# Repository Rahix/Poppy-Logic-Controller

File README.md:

<h2 align="center">Poppy Logic Controller</h2>

---

The _Poppy Logic Controller_ is a budget PLC (Programmable Logic Controller).
Importantly, it is only an I/O board without any PLC programming environment
(so far).  It isn't designed to be super robust but instead to use minimal
components while still staying compatible with standard industrial 24V DC
control systems.

I release the _Poppy Logic Controller_ as open hardware in hopes that others
who need a cheap solution for controlling industrial 24V DC equipment find it
useful.  _This is not a commercially viable PLC alternative._

If you want to know more about the background of this project and details of
the design, you might be interested in the blog post I wrote about it: [**Poppy
Logic Controller**][poppy-blog]

### Features
- Designed for 24V DC systems as most commonly found in modern controls
  applications.
- 16 DI (digital inputs) in a **Sinking Input** configuration.
- 16 DO (digital outputs) in a **Sinking Output** configuration.
- Firmware stubs in [Rust][fw-rust], [MicroPython][fw-mp], and [IEC 61131-3
  _Structured Text_][fw-iec].

<small>Learn more about sinking/sourcing I/O [here][realpars-input] and
[here][realpars-output] or from [my blog-post about this
project][poppy-blog].</small>

### Non-Features
- I/Os are **not** galvanically isolated.  Honestly, the isolators would
  probably be more expensive than the MCU so there is not much incentive to
  implement isolation anyway.
- The board currently does not have any communication interfaces apart from the
  Pico's USB port.  If you need to interface with anything, you might need to
  either update the board design or connect an additional mod onto the `J12`
  header.

### Building Your Own
Rendered versions of the schematic and BOM can be found here:

- [Rendered Schematic](./Docs/PoppyIO.pdf)
- [Rendered BOM](https://rahix.github.io/Poppy-Logic-Controller/Docs/PoppyIO_bom_D.html)
- [Rendered Interactive BOM](https://rahix.github.io/Poppy-Logic-Controller/Docs/PoppyIO_ibom_D.html)

#### Parts
Supplier for almost all parts of this project was [Reichelt Elektronik] (no
affiliation or sponsorship here, purely personal choice).  I've tried
reconstructing the BOM with all the Reichelt SKUs so you can painlessly get all
you need from one place if you so desire.  There is a column in the BOMs linked
above with all the information you need.

#### Additional Components
Beyond the PCB's BOM, you will need a few more components.  After all, you
probably want the nice feeling of mounting your controller on a DIN-rail, don't
you?

1. The enclosure, which is an `APRA-NORM 449-360-65` (Reichelt `APRA DB6 OBK`)
2. Optionally, a lid for the enclosure, like `APRA-NORM 449-360-12` (Reichelt
   `APRA 449-360-12`). Also available in other colors.
3. A few (2) jumpers (Reichelt `JUMPER 2,54 SW`)

#### Hardware Revisions
In the design files, you'll find the latest revision **D**.  I suggest using
that one although it is not exactly the version I have built.  My (2) boards
are built from revision **B** with one populated like revision **C** and one
populated like revision **D**.  You can read the [changelog][poppy-changelog]
for details of the differences.

#### Programming It
This repository contains a bare-bones firmware in Rust and MicroPython to get
started.  Or, if you have a background in automation, you can program the Poppy
Logic Controller in _ST_ (_Structured Text_) using the IEC 61131-3 firmware.
Check the READMEs for more info on that:

- [Firmware-Rust][fw-rust]
- [Firmware-MicroPython][fw-mp]
- [Firmware-IEC][fw-iec]

#### Not using the Pico
If you need a different microcontroller, you can drop the Raspberry Pi Pico and
instead solder the `J12` header.  You can then connect whatever controller you
desire and use the I²C bus (and interrupt lines) to interact with the I/O.

---

If you want to build your own but you are unsure or you have questions about
anything, feel free to contact me to get it sorted out!

## License
- The hardware design files (everything in `Hardware/`) are licensed under the
  [CERN-OHL-W](LICENSE-HARDWARE).
- The firmware stubs (everything in `Firmware-*/`) are licensed under
  [MIT](LICENSE-SOFTWARE).

[Reichelt Elektronik]: https://www.reichelt.de/
[poppy-blog]: https://blog.rahix.de/poppy-logic-controller/
[poppy-changelog]: ./Hardware/PoppyIO/CHANGELOG.md
[realpars-input]: https://realpars.com/sinking-and-sourcing/
[realpars-output]: https://realpars.com/sinking-output/
[fw-rust]: ./Firmware-Rust/
[fw-mp]: ./Firmware-MicroPython/
[fw-iec]: ./Firmware-IEC/

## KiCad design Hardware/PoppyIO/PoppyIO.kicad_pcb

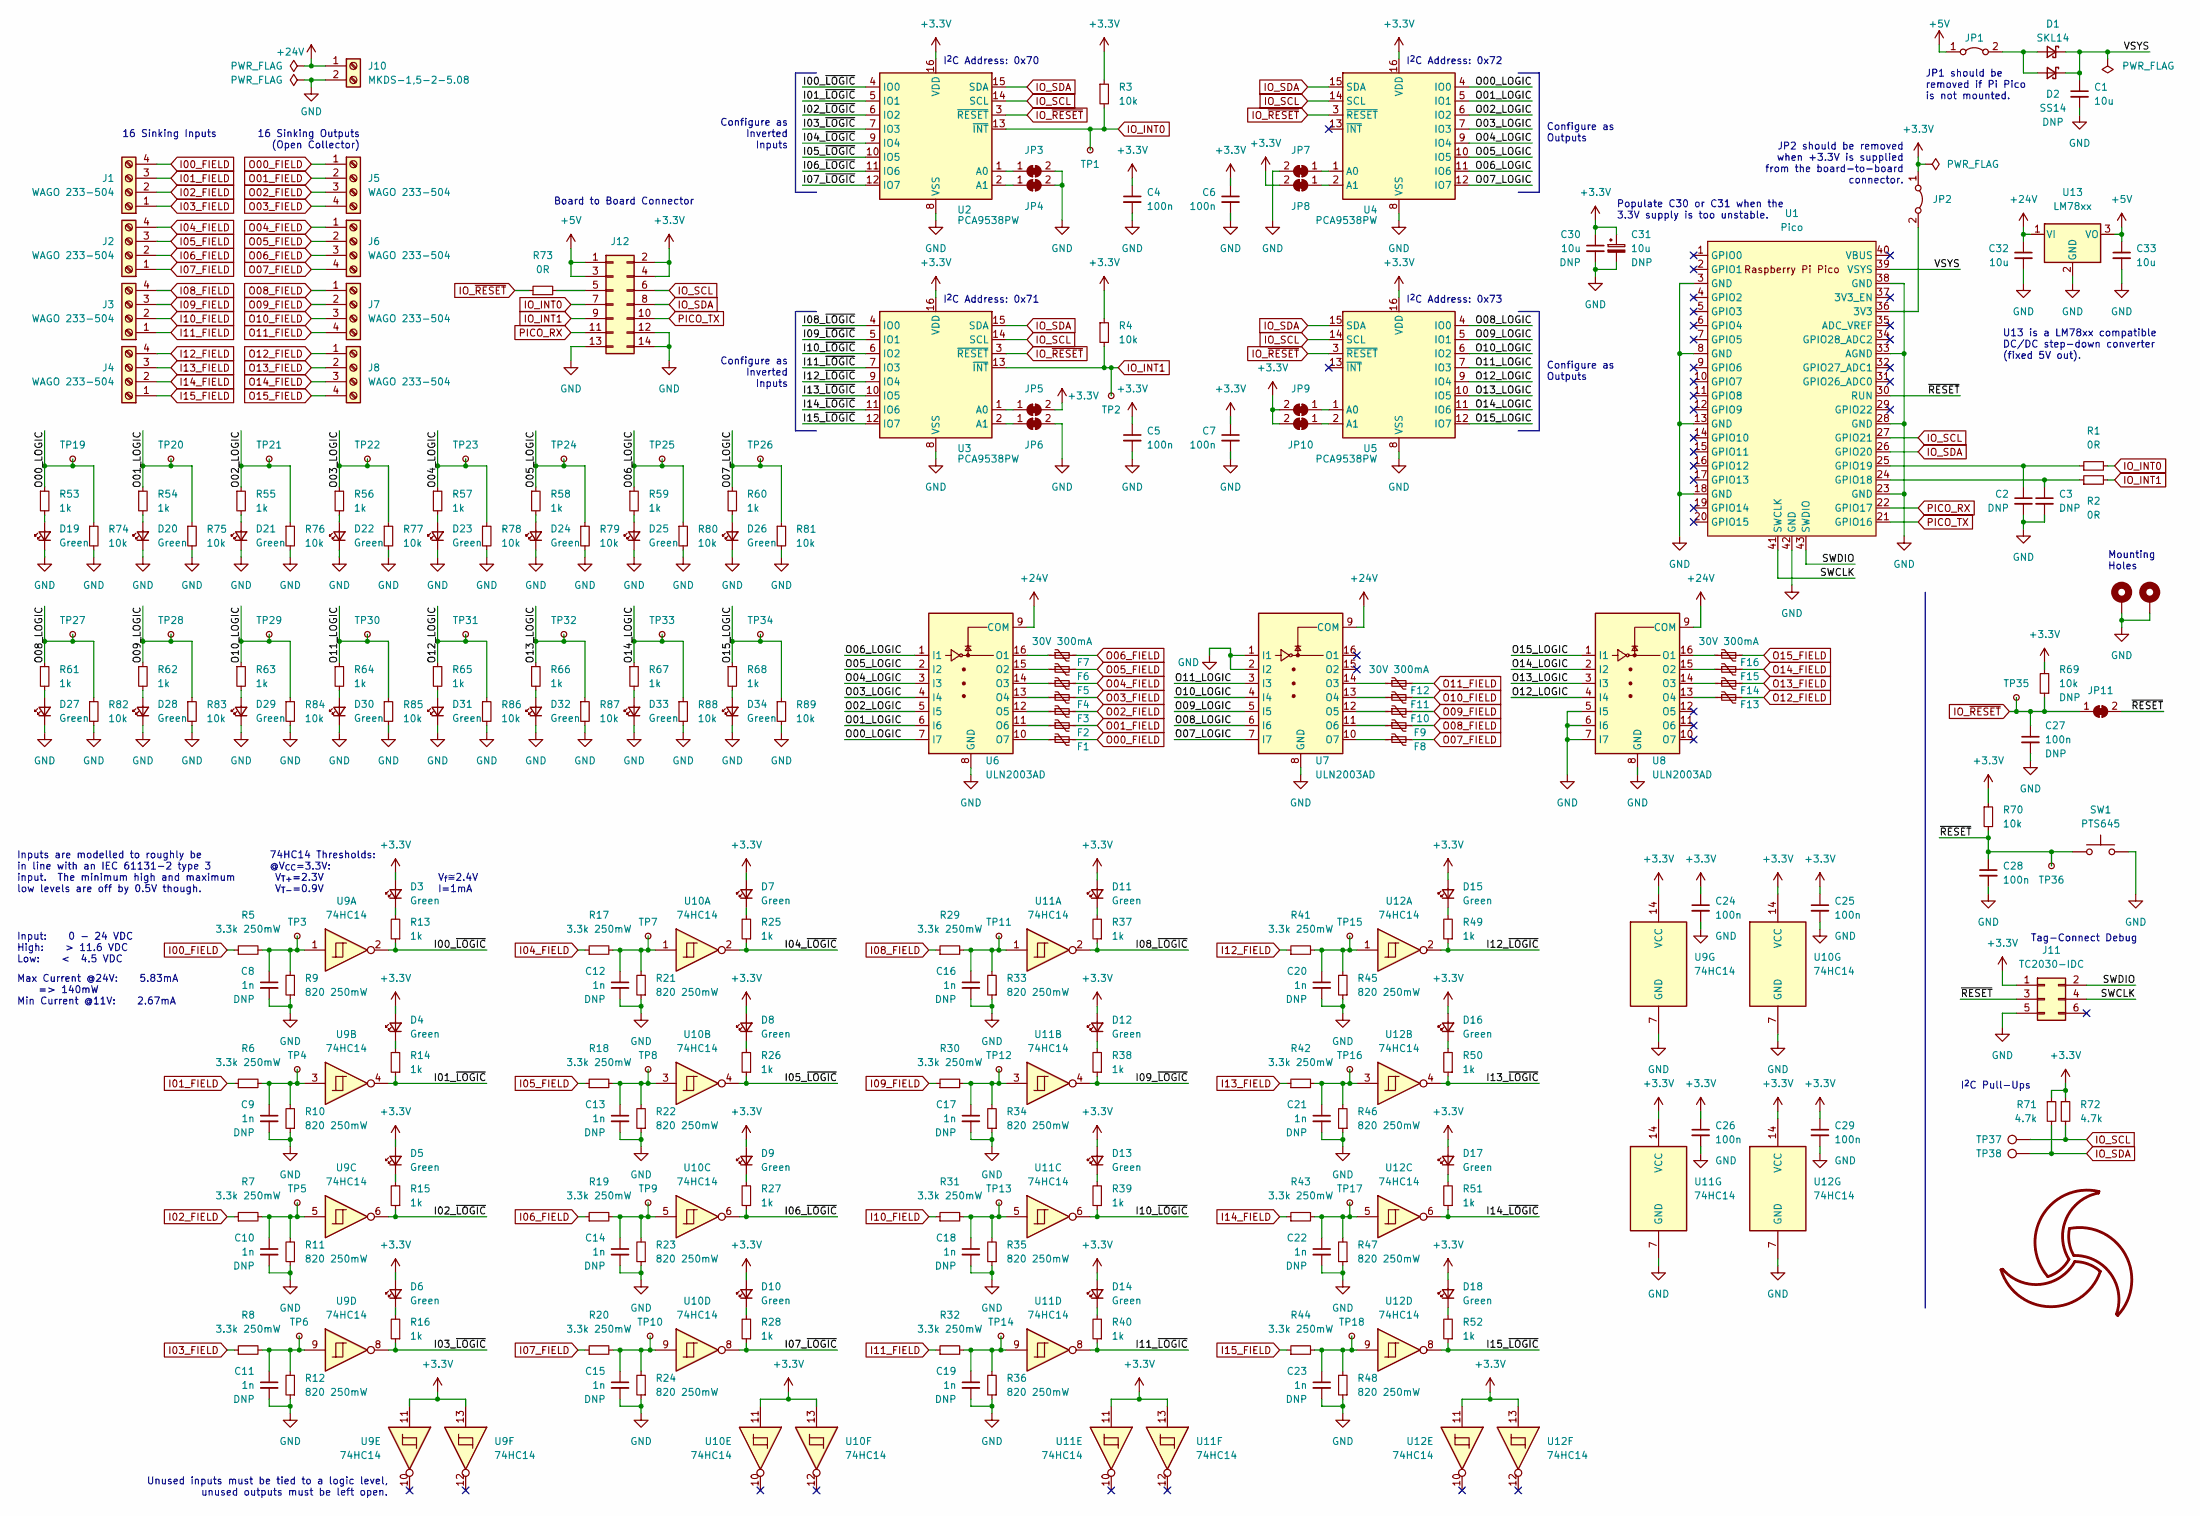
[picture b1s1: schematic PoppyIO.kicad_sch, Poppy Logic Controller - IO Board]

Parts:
C1, C30, C32, C33: 10u; C_1210_3225Metric
C2, C3: C_0603_1608Metric_Pad1.08x0.95mm_HandSolder
C4, C5, C6, C7, C24, C25, C26, C27, C28, C29: 100n; C_0603_1608Metric_Pad1.08x0.95mm_HandSolder
C8, C9, C10, C11, C12, C13, C14, C15, C16, C17, C18, C19, C20, C21, C22, C23: 1n; C_0805_2012Metric
C31: 10u; CP_Radial_D5.0mm_P2.50mm
D1: SKL14; D_SOD-123
D2: SS14; D_SMA
D3, D4, D5, D6, D7, D8, D9, D10, D11, D12, D13, D14, D15, D16, D17, D18, D19, D20, D21, D22, D23, D24, D25, D26, D27, D28, D29, D30, D31, D32, D33, D34: Green; LED_0805_2012Metric_Pad1.15x1.40mm_HandSolder
F1, F2, F3, F4, F5, F6, F7, F8, F9, F10, F11, F12, F13, F14, F15, F16: 30V 300mA; Fuse_1210_3225Metric_Pad1.42x2.65mm_HandSolder
H1, H2: MountingHole_Pad; MountingHole_3.2mm_M3_Pad_Via
J1, J2, J3, J4, J5, J6, J7, J8: WAGO 233-504; WAGO_233-204
J10: MKDS-1,5-2-5.08; TerminalBlock_Phoenix_MKDS-1,5-2-5.08_1x02_P5.08mm_Horizont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
J11: TC2030-IDC; Tag-Connect_TC2030-IDC-FP_2x03_P1.27mm_Vertical
J12: Conn_02x07_Odd_Even; IDC-Header_2x07_P2.54mm_Vertical
JP1, JP2: PinHeader_1x02_P2.54mm_Vertical
JP3, JP4, JP5, JP6, JP7, JP8, JP9, JP10, JP11: SolderJumper_2_Bridged; SolderJumper-2_P1.3mm_Bridged_RoundedPad1.0x1.5mm
R1, R2, R73: 0R; R_0603_1608Metric
R3, R4, R69, R70, R74, R75, R76, R77, R78, R79, R80, R81, R82, R83, R84, R85, R86, R87, R88, R89: 10k; R_0603_1608Metric
R5, R6, R7, R8, R17, R18, R19, R20, R29, R30, R31, R32, R41, R42, R43, R44: 3.3k 250mW; R_1206_3216Metric
R9, R10, R11, R12, R21, R22, R23, R24, R33, R34, R35, R36, R45, R46, R47, R48: 820 250mW; R_1206_3216Metric
R13, R14, R15, R16, R25, R26, R27, R28, R37, R38, R39, R40, R49, R50, R51, R52, R53, R54, R55, R56, R57, R58, R59, R60, R61, R62, R63, R64, R65, R66, R67, R68: 1k; R_0603_1608Metric
R71, R72: 4.7k; R_0603_1608Metric_Pad0.98x0.95mm_HandSolder
SW1: PTS645; SW_SPST_PTS645
SYM1: SYM_Rahix
TP1, TP2, TP3, TP4, TP5, TP6, TP7, TP8, TP9, TP10, TP11, TP12, TP13, TP14, TP15, TP16, TP17, TP18, TP19, TP20, TP21, TP22, TP23, TP24, TP25, TP26, TP27, TP28, TP29, TP30, TP31, TP32, TP33, TP34, TP35, TP36: TestPoint_Small; TestPoint_Pad_D1.5mm
TP37, TP38: TestPoint; TestPoint_Pad_D1.5mm
U1: Pico; RPi_Pico_SMD_TH
U2, U3, U4, U5: PCA9538PW; TSSOP-16_4.4x5mm_P0.65mm
U6, U7, U8: ULN2003AD; SOIC-16_3.9x9.9mm_P1.27mm
U9, U10, U11, U12: 74HC14; SOIC-14_3.9x8.7mm_P1.27mm
U13: LM78xx; TO-220-3_Vertical_Clearance

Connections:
+3.3V: C4.1, C5.1, C6.1, C7.1, C24.1, C25.1, C26.1, C29.1, C30.1, C31.1, D3.2 (A), D4.2 (A), D5.2 (A), D6.2 (A), D7.2 (A), D8.2 (A), D9.2 (A), D10.2 (A), D11.2 (A), D12.2 (A), D13.2 (A), D14.2 (A), D15.2 (A), D16.2 (A), D17.2 (A), D18.2 (A), J11.1, J12.2, J12.4, JP2.1 (A), JP5.2 (B), JP8.2 (B), JP9.2 (B), JP10.2 (B), R3.1, R4.1, R69.2, R70.1, R71.1, R72.1, U2.16 (VDD), U3.16 (VDD), U4.16 (VDD), U5.16 (VDD), U9.11, U9.13, U9.14 (VCC), U10.11, U10.13, U10.14 (VCC), U11.11, U11.13, U11.14 (VCC), U12.11, U12.13, U12.14 (VCC)
+5V: C33.1, J12.1, J12.3, JP1.1 (A), U13.3 (VO)
+24V: C32.1, J10.1, U6.9 (COM), U7.9 (COM), U8.9 (COM), U13.1 (VI)
/I00_~LOGIC: R13.1, U2.4 (IO0), U9.2
/I01_~LOGIC: R14.1, U2.5 (IO1), U9.4
/I02_~LOGIC: R15.1, U2.6 (IO2), U9.6
/I03_~LOGIC: R16.1, U2.7 (IO3), U9.8
/I04_~LOGIC: R25.1, U2.9 (IO4), U10.2
/I05_~LOGIC: R26.1, U2.10 (IO5), U10.4
/I06_~LOGIC: R27.1, U2.11 (IO6), U10.6
/I07_~LOGIC: R28.1, U2.12 (IO7), U10.8
/I08_~LOGIC: R37.1, U3.4 (IO0), U11.2
/I09_~LOGIC: R38.1, U3.5 (IO1), U11.4
/I10_~LOGIC: R39.1, U3.6 (IO2), U11.6
/I11_~LOGIC: R40.1, U3.7 (IO3), U11.8
/I12_~LOGIC: R49.1, U3.9 (IO4), U12.2
/I13_~LOGIC: R50.1, U3.10 (IO5), U12.4
/I14_~LOGIC: R51.1, U3.11 (IO6), U12.6
/I15_~LOGIC: R52.1, U3.12 (IO7), U12.8
/O00_LOGIC: R53.1, R74.1, TP19.1, U4.4 (IO0), U6.7 (I7)
/O01_LOGIC: R54.1, R75.1, TP20.1, U4.5 (IO1), U6.6 (I6)
/O02_LOGIC: R55.1, R76.1, TP21.1, U4.6 (IO2), U6.5 (I5)
/O03_LOGIC: R56.1, R77.1, TP22.1, U4.7 (IO3), U6.4 (I4)
/O04_LOGIC: R57.1, R78.1, TP23.1, U4.9 (IO4), U6.3 (I3)
/O05_LOGIC: R58.1, R79.1, TP24.1, U4.10 (IO5), U6.2 (I2)
/O06_LOGIC: R59.1, R80.1, TP25.1, U4.11 (IO6), U6.1 (I1)
/O07_LOGIC: R60.1, R81.1, TP26.1, U4.12 (IO7), U7.7 (I7)
/O08_LOGIC: R61.1, R82.1, TP27.1, U5.4 (IO0), U7.6 (I6)
/O09_LOGIC: R62.1, R83.1, TP28.1, U5.5 (IO1), U7.5 (I5)
/O10_LOGIC: R63.1, R84.1, TP29.1, U5.6 (IO2), U7.4 (I4)
/O11_LOGIC: R64.1, R85.1, TP30.1, U5.7 (IO3), U7.3 (I3)
/O12_LOGIC: R65.1, R86.1, TP31.1, U5.9 (IO4), U8.4 (I4)
/O13_LOGIC: R66.1, R87.1, TP32.1, U5.10 (IO5), U8.3 (I3)
/O14_LOGIC: R67.1, R88.1, TP33.1, U5.11 (IO6), U8.2 (I2)
/O15_LOGIC: R68.1, R89.1, TP34.1, U5.12 (IO7), U8.1 (I1)
/SWCLK: J11.4, U1.41 (SWCLK)
/SWDIO: J11.2, U1.43 (SWDIO)
/VSYS: C1.1, D1.1 (K), D2.1 (K), U1.39 (VSYS)
/~RESET: C28.1, J11.3, JP11.2 (B), R70.2, SW1.1, TP36.1, U1.30 (RUN)
GND: C1.2, C2.2, C3.2, C4.2, C5.2, C6.2, C7.2, C8.2, C9.2, C10.2, C11.2, C12.2, C13.2, C14.2, C15.2, C16.2, C17.2, C18.2, C19.2, C20.2, C21.2, C22.2, C23.2, C24.2, C25.2, C26.2, C27.2, C28.2, C29.2, C30.2, C31.2, C32.2, C33.2, D19.1 (K), D20.1 (K), D21.1 (K), D22.1 (K), D23.1 (K), D24.1 (K), D25.1 (K), D26.1 (K), D27.1 (K), D28.1 (K), D29.1 (K), D30.1 (K), D31.1 (K), D32.1 (K), D33.1 (K), D34.1 (K), H1.1, H2.1, J10.2, J11.5, J12.12, J12.13, J12.14, JP3.2 (B), JP4.2 (B), JP6.2 (B), JP7.2 (B), R9.1, R10.1, R11.1, R12.1, R21.1, R22.1, R23.1, R24.1, R33.1, R34.1, R35.1, R36.1, R45.1, R46.1, R47.1, R48.1, R74.2, R75.2, R76.2, R77.2, R78.2, R79.2, R80.2, R81.2, R82.2, R83.2, R84.2, R85.2, R86.2, R87.2, R88.2, R89.2, SW1.2, U1.3 (GND), U1.8 (GND), U1.13 (GND), U1.18 (GND), U1.23 (GND), U1.28 (GND), U1.33 (AGND), U1.38 (GND), U1.42 (GND), U2.8 (VSS), U3.8 (VSS), U4.8 (VSS), U5.8 (VSS), U6.8 (GND), U7.1 (I1), U7.2 (I2), U7.8 (GND), U8.5 (I5), U8.6 (I6), U8.7 (I7), U8.8 (GND), U9.7 (GND), U10.7 (GND), U11.7 (GND), U12.7 (GND), U13.2 (GND)
I00_FIELD: J1.4, R5.1
I01_FIELD: J1.3, R6.1
I02_FIELD: J1.2, R7.1
I03_FIELD: J1.1, R8.1
I04_FIELD: J2.4, R17.1
I05_FIELD: J2.3, R18.1
I06_FIELD: J2.2, R19.1
I07_FIELD: J2.1, R20.1
I08_FIELD: J3.4, R29.1
I09_FIELD: J3.3, R30.1
I10_FIELD: J3.2, R31.1
I11_FIELD: J3.1, R32.1
I12_FIELD: J4.4, R41.1
I13_FIELD: J4.3, R42.1
I14_FIELD: J4.2, R43.1
I15_FIELD: J4.1, R44.1
IO_INT0: J12.7, R1.2, R3.2, TP1.1, U2.13 (~INT)
IO_INT1: J12.9, R2.2, R4.2, TP2.1, U3.13 (~INT)
IO_SCL: J12.6, R72.2, TP37.1, U1.27 (GPIO21), U2.14 (SCL), U3.14 (SCL), U4.14 (SCL), U5.14 (SCL)
IO_SDA: J12.8, R71.2, TP38.1, U1.26 (GPIO20), U2.15 (SDA), U3.15 (SDA), U4.15 (SDA), U5.15 (SDA)
IO_~RESET: C27.1, JP11.1 (A), R69.1, R73.1, TP35.1, U2.3 (~RESET), U3.3 (~RESET), U4.3 (~RESET), U5.3 (~RESET)
unnamed: C2.1, R1.1, U1.25 (GPIO19)
unnamed: C3.1, R2.1, U1.24 (GPIO18)
unnamed: C8.1, R5.2, R9.2, TP3.1, U9.1
unnamed: C9.1, R6.2, R10.2, TP4.1, U9.3
unnamed: C10.1, R7.2, R11.2, TP5.1, U9.5
unnamed: C11.1, R8.2, R12.2, TP6.1, U9.9
unnamed: C12.1, R17.2, R21.2, TP7.1, U10.1
unnamed: C13.1, R18.2, R22.2, TP8.1, U10.3
unnamed: C14.1, R19.2, R23.2, TP9.1, U10.5
unnamed: C15.1, R20.2, R24.2, TP10.1, U10.9
unnamed: C16.1, R29.2, R33.2, TP11.1, U11.1
unnamed: C17.1, R30.2, R34.2, TP12.1, U11.3
unnamed: C18.1, R31.2, R35.2, TP13.1, U11.5
unnamed: C19.1, R32.2, R36.2, TP14.1, U11.9
unnamed: C20.1, R41.2, R45.2, TP15.1, U12.1
unnamed: C21.1, R42.2, R46.2, TP16.1, U12.3
unnamed: C22.1, R43.2, R47.2, TP17.1, U12.5
unnamed: C23.1, R44.2, R48.2, TP18.1, U12.9
unnamed: D1.2 (A), D2.2 (A), JP1.2 (B)
unnamed: D3.1 (K), R13.2
unnamed: D4.1 (K), R14.2
unnamed: D5.1 (K), R15.2
unnamed: D6.1 (K), R16.2
unnamed: D7.1 (K), R25.2
unnamed: D8.1 (K), R26.2
unnamed: D9.1 (K), R27.2
unnamed: D10.1 (K), R28.2
unnamed: D11.1 (K), R37.2
unnamed: D12.1 (K), R38.2
unnamed: D13.1 (K), R39.2
unnamed: D14.1 (K), R40.2
unnamed: D15.1 (K), R49.2
unnamed: D16.1 (K), R50.2
unnamed: D17.1 (K), R51.2
unnamed: D18.1 (K), R52.2
unnamed: D19.2 (A), R53.2
unnamed: D20.2 (A), R54.2
unnamed: D21.2 (A), R55.2
unnamed: D22.2 (A), R56.2
unnamed: D23.2 (A), R57.2
unnamed: D24.2 (A), R58.2
unnamed: D25.2 (A), R59.2
unnamed: D26.2 (A), R60.2
unnamed: D27.2 (A), R61.2
unnamed: D28.2 (A), R62.2
unnamed: D29.2 (A), R63.2
unnamed: D30.2 (A), R64.2
unnamed: D31.2 (A), R65.2
unnamed: D32.2 (A), R66.2
unnamed: D33.2 (A), R67.2
unnamed: D34.2 (A), R68.2
unnamed: F1.1, U6.10 (O7)
unnamed: F2.1, U6.11 (O6)
unnamed: F3.1, U6.12 (O5)
unnamed: F4.1, U6.13 (O4)
unnamed: F5.1, U6.14 (O3)
unnamed: F6.1, U6.15 (O2)
unnamed: F7.1, U6.16 (O1)
unnamed: F8.1, U7.10 (O7)
unnamed: F9.1, U7.11 (O6)
unnamed: F10.1, U7.12 (O5)
unnamed: F11.1, U7.13 (O4)
unnamed: F12.1, U7.14 (O3)
unnamed: F13.1, U8.13 (O4)
unnamed: F14.1, U8.14 (O3)
unnamed: F15.1, U8.15 (O2)
unnamed: F16.1, U8.16 (O1)
unnamed: J12.5, R73.2
unnamed: JP2.2 (B), U1.36 (3V3)
unnamed: JP3.1 (A), U2.1 (A0)
unnamed: JP4.1 (A), U2.2 (A1)
unnamed: JP5.1 (A), U3.1 (A0)
unnamed: JP6.1 (A), U3.2 (A1)
unnamed: JP7.1 (A), U4.1 (A0)
unnamed: JP8.1 (A), U4.2 (A1)
unnamed: JP9.1 (A), U5.1 (A0)
unnamed: JP10.1 (A), U5.2 (A1)
O00_FIELD: F1.2, J5.1
O01_FIELD: F2.2, J5.2
O02_FIELD: F3.2, J5.3
O03_FIELD: F4.2, J5.4
O04_FIELD: F5.2, J6.1
O05_FIELD: F6.2, J6.2
O06_FIELD: F7.2, J6.3
O07_FIELD: F8.2, J6.4
O08_FIELD: F9.2, J7.1
O09_FIELD: F10.2, J7.2
O10_FIELD: F11.2, J7.3
O11_FIELD: F12.2, J7.4
O12_FIELD: F13.2, J8.1
O13_FIELD: F14.2, J8.2
O14_FIELD: F15.2, J8.3
O15_FIELD: F16.2, J8.4
PICO_RX: J12.11, U1.22 (GPIO17)
PICO_TX: J12.10, U1.21 (GPIO16)

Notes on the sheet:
Configure as Outputs
16 Sinking Inputs
Input: 0 - 24 VDC High: > 11.6 VDC Low: < 4.5 VDC
U13 is a LM78xx compatible DC/DC step-down converter (fixed 5V out).
JP1 should be removed if Pi Pico is not mounted.
Inputs are modelled to roughly be in line with an IEC 61131-2 type 3 input. The minimum high and maximum low levels are off by 0.5V though.
Unused inputs must be tied to a logic level, unused outputs must be left open.
I^{2}C Address: 0x70
I^{2}C Address: 0x73
I^{2}C Address: 0x72
74HC14 Thresholds: @V_{CC}=3.3V: V_{T+}=2.3V V_{T-}=0.9V
I^{2}C Address: 0x71
Tag-Connect Debug
Max Current @24V: 5.83mA => 140mW Min Current @11V: 2.67mA
Board to Board Connector
Configure as Inverted Inputs
I^{2}C Pull-Ups
16 Sinking Outputs (Open Collector)
Populate C30 or C31 when the 3.3V supply is too unstable.
V_{f}≅2.4V I=1mA
JP2 should be removed when +3.3V is supplied from the board-to-board connector.
Mounting Holes

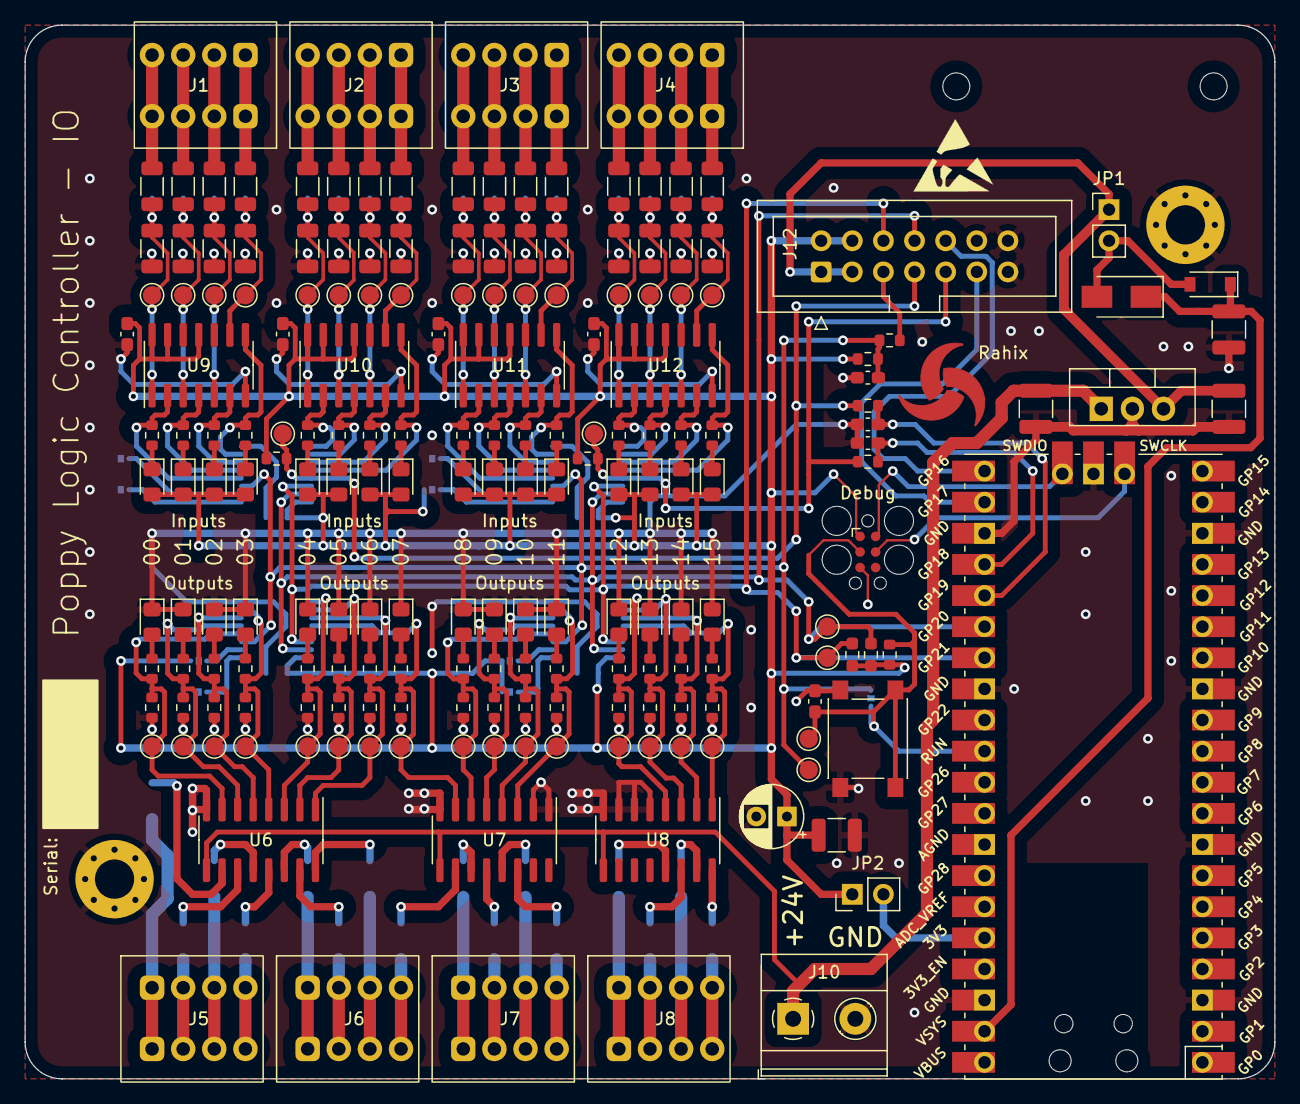
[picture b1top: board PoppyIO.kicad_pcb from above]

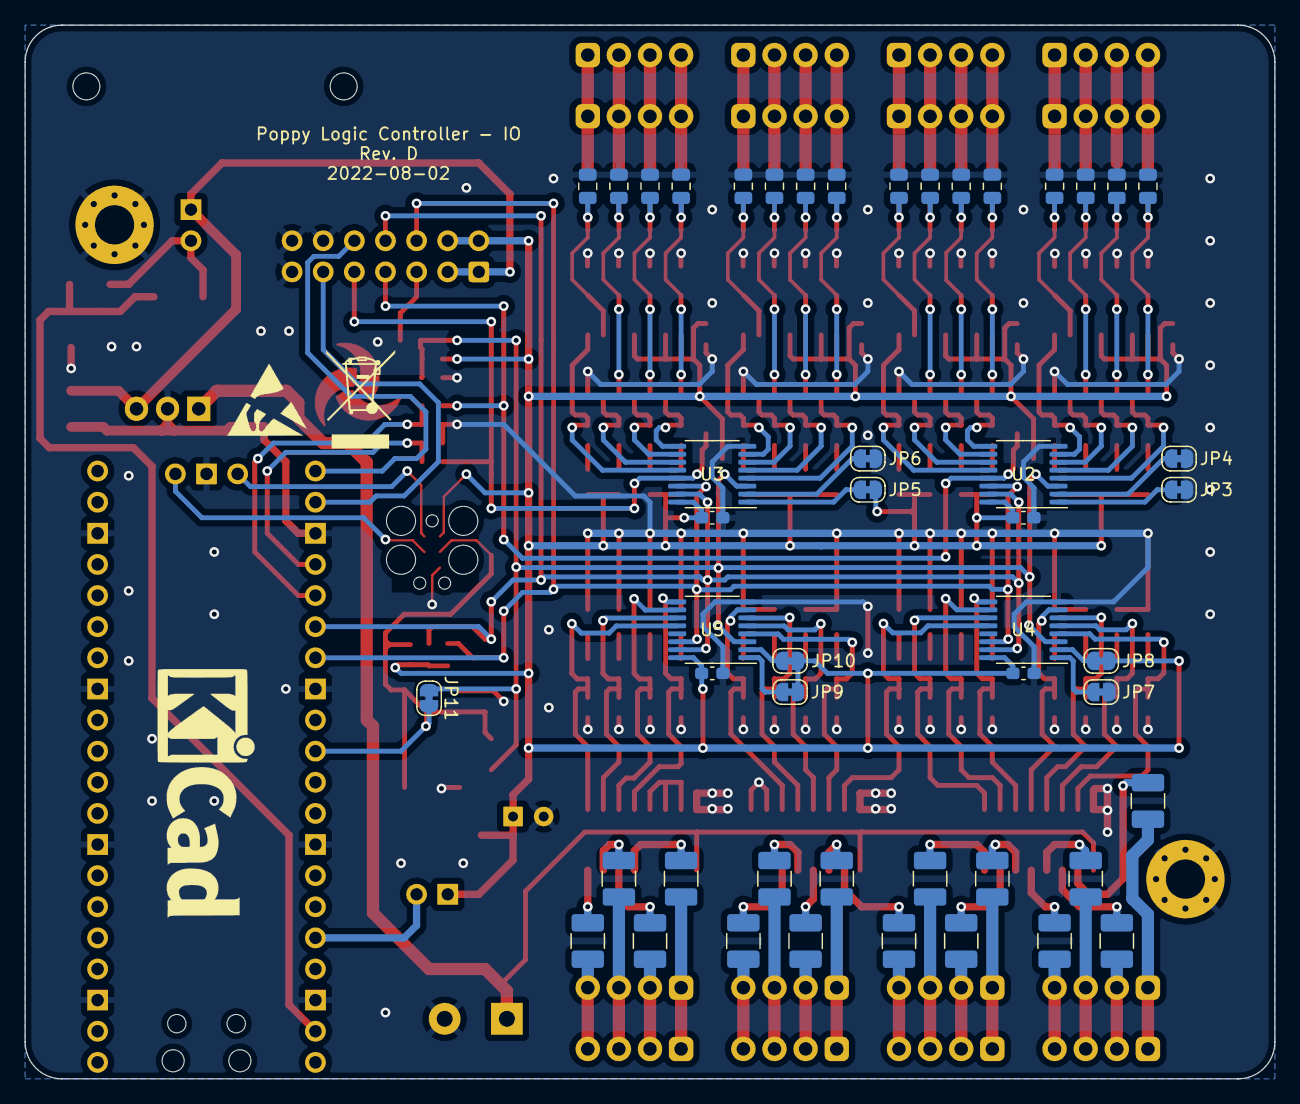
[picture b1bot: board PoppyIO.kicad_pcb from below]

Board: 2 copper layers, 102.0 x 86.0 mm, 249 parts (49 on the bottom side), 156 nets.

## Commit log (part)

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2022-04-01 Initial
2022-04-01 hw: lib: Import RP-Pico library
    Import symbols and footprints for the Raspberry-Pi Pico from
    https://github.com/ncarandini/KiCad-RP-Pico
    at commit dc6f9b9f213d ("Update Install instructions.md").
2022-04-01 hw: lib: pico: Update 3D model path
2022-04-01 hw: io: Add libraries
2022-04-01 hw: io: Work on 24 VDC inputs and outputs
2022-04-01 hw: io: Updates
2022-04-01 hw: io: Single sheet
2022-04-01 hw: io: Output drivers and other things
2022-04-01 hw: lib: Add WAGO 233-204/504 footprint
2022-04-01 hw: io: Add poppy library
2022-04-02 hw: lib: Update pico pin types
    The 3V3 pin is a power output and one GND pin was erroneously specified
    as "bidirectional".
2022-04-02 hw: io: Annotate
2022-04-02 hw: io: Footprints
2022-04-02 hw: ui: Adjust connector pin ordering
2022-04-02 hw: io: More layout improvements
    Reorder driver pins
2022-04-03 hw: lib: Use official pico 3D model
    This model is much simpler and thus loading times are much shorter.
2022-04-03 hw: io: Update footprints
2022-04-03 hw: io: Update PCB
2022-04-03 hw: io: PCB Updates
2022-04-03 hw: io: More updates
2022-04-06 hw: io: Switch to ULN2003AD
2022-04-10 hw: io: Updates & clean PCB
2022-04-13 hw: lib: Add PCA9538PW symbol
2022-04-13 hw: Update gitignore
2022-04-13 hw: io: Update schematic
    Different input stage
2022-04-14 hw: io: ERC fixes
2022-04-14 hw: io: Add KiBOM config
2022-04-14 hw: io: Update schematic
2022-04-14 hw: io: Use one more inverter IC
    This should make layout easier
2022-04-14 hw: io: Different fuses
2022-04-15 hw: io: Unused ULN2003 inputs
    Tie them to GND.
2022-04-22 hw: io: Start PCB layout for real this time
2022-04-22 hw: io: sch: Reorder series resistors for output LEDs
    This helps with routing.
2022-04-22 hw: io: Board settings
2022-04-22 hw: io: PCB layout
2022-04-22 hw: io: More PCB layout
2022-04-23 hw: io: Updae PCB and DRC fixes
2022-04-23 hw: io: Update JP2
    shouldn't be a solder jumper
2022-04-23 hw: io: Add footprints for 3V3 decoupling caps
2022-04-23 hw: io: Add artwork
2022-04-23 hw: io: More PCB tweaks
2022-04-24 hw: lib: Add footprint for TO-220-3 with clearance
    This allows to mount LM78xx regulators but also drop-in replacements
    like Gaptec's LMS78 or LMO78 DC/DC step-down supplies.
2022-04-24 hw: io: Add footprints for 24V -> 5V regulator
    In the future, maybe we will want to switch to a unified 24V supply.
    Add footprints for installing a regulator or SPMS to do this.
2022-04-24 hw: io: pcb: Fabrication layers
2022-04-24 hw: io: Final touches and prepare revision A
2022-04-25 hw: io: Switch to 14-pin IDC
2022-06-26 hw: io: Fix wrong DI resistors
    Copy-paste error - the calculations projected an 820Ω resistor but I
    accidentally used 680Ω instead. This still works but has different
    limiting values...
2022-08-02 hw: io: Schematic updates
    - Drop DNP config from LM78xx regulator and capacitors.
    - Removed screw-terminal J9 for external 5V supply.
    - Switched +24VDC screw-terminal to 2-pin variant.
    - Documented J2 meaning.
2022-08-02 hw: io: Mirror schematic changes on PCB
2022-08-02 hw: io: PCB cleanup and update J10 footprint
    Choose an appropriate screw-terminal for J10 which has 2 pins and 5.08mm
    pitch.
2022-08-02 hw: io: Add Reichelt SKUs for all applicable parts
2022-08-02 Update CHANGELOG
2022-08-06 hw: io: Generate revision D documents
    - Interactive BOM
    - HTML BOM
    - Schematic PDF
2022-08-07 fw: Add bare-bones MicroPython firmware
    This is a sample driver for writing controls programs for the Poppy
    Logic Controller in MicroPython.
2022-08-07 fw: Add bare-bones Rust firmware
    This is a sample firmware for writing a control program for the Poppy
    Logic Controller in Rust. It uses the `port-expander` [1] crate to
    interact with the I/O expanders.
    [1]: https://crates.io/crates/port-expander
2022-08-07 Revision D Rendered Documents
2022-08-07 Add README and licenses
    Document this project...
2022-08-21 Add the beginnings of an IEC firmware
    This firmware allows writing programs for the Poppy Logic Controller in
    IEC 61131-3 languages like ST (Structured Text).
2022-08-21 fw: iec: Cleanup driver implementation
2022-08-21 fw: iec: Cleanup the ST program
    Proper style and naming conventions. Add some comments.
2022-09-01 fw: iec: Integrate modbus RTU server
    The server is not connected to the PLC runtime yet so register changes
    will not have any effect. It is visible as a USB-Serial device over
    USB.
2022-09-01 fw: iec: Integrate modbus with PLC runtime
    Make memory bits %MX00 - %MX15 and memory words %MW00 - %MW15 available
    via modbus coils 0 - 15 and holding registers 0 - 15 respectively.
    Additionally, expose the state of all inputs in discrete inputs 0 - 15
    and the state of all outputs in descrete inputs 16 - 31.
2022-09-01 fw: iec: Use modbus in example code
    Add modbus coils 0 and 1 as alternative start and stop buttons which can
    be remotely controlled and have the same function as the local inputs.
2022-09-01 fw: iec: Document Modbus interface
2022-09-01 Ignore pymodbus history file
2022-09-01 fw: iec: Document Modbus GUI
2022-09-05 fw: iec: Use upstream rmodbus
2023-01-05 fw: Apply rustfmt
2023-01-05 Enable GitHub Dependabot
2023-01-05 ci: Setup GitHub Actions
2023-01-05 fw: iec: Drop unused delay timer
2023-01-05 build(deps): bump shared-bus from 0.2.4 to 0.2.5 in /Firmware-Rust
    Bumps [shared-bus](https://github.com/Rahix/shared-bus) from 0.2.4 to 0.2.5.
    - [Release notes](https://github.com/Rahix/shared-bus/releases)
    - [Changelog](https://github.com/Rahix/shared-bus/blob/main/CHANGELOG.md)
    - [Commits](https://github.com/Rahix/shared-bus/compare/v0.2.4...v0.2.5)
    ---
    updated-dependencies:
2023-01-05 build(deps): bump paste from 1.0.8 to 1.0.11 in /Firmware-IEC
    Bumps [paste](https://github.com/dtolnay/paste) from 1.0.8 to 1.0.11.
    - [Release notes](https://github.com/dtolnay/paste/releases)
    - [Commits](https://github.com/dtolnay/paste/compare/1.0.8...1.0.11)
    ---
    updated-dependencies:
    - dependency-name: paste
2023-01-05 fw: rust: Bump shared-bus from 0.2.4 to 0.2.5
2023-01-05 fw: rust: Bump cortex-m from 0.7.5 to 0.7.7
2023-01-05 fw: iec: Bump paste from 1.0.8 to 1.0.11
2023-01-05 build(deps): bump cortex-m-rt from 0.7.1 to 0.7.2 in /Firmware-Rust
    Bumps [cortex-m-rt](https://github.com/rust-embedded/cortex-m) from 0.7.1 to 0.7.2.
    - [Release notes](https://github.com/rust-embedded/cortex-m/releases)
    - [Changelog](https://github.com/rust-embedded/cortex-m/blob/master/CHANGELOG.md)
    - [Commits](https://github.com/rust-embedded/cortex-m/compare/v0.7.1...v0.7.2)
    ---
    updated-dependencies:
2023-01-05 build(deps): bump cortex-m-rt from 0.7.1 to 0.7.2 in /Firmware-IEC
    Bumps [cortex-m-rt](https://github.com/rust-embedded/cortex-m) from 0.7.1 to 0.7.2.
    - [Release notes](https://github.com/rust-embedded/cortex-m/releases)
    - [Changelog](https://github.com/rust-embedded/cortex-m/blob/master/CHANGELOG.md)
    - [Commits](https://github.com/rust-embedded/cortex-m/compare/v0.7.1...v0.7.2)
    ---
    updated-dependencies:
2023-01-05 fw: iec: Bump cortex-m-rt from 0.7.1 to 0.7.2
2023-01-05 fw: rust: Bump cortex-m-rt from 0.7.1 to 0.7.2
2023-01-05 fw: iec: Bump cc from 1.0.73 to 1.0.78
2023-01-05 build(deps): bump cortex-m from 0.7.5 to 0.7.7 in /Firmware-IEC
    Bumps [cortex-m](https://github.com/rust-embedded/cortex-m) from 0.7.5 to 0.7.7.
    - [Release notes](https://github.com/rust-embedded/cortex-m/releases)
    - [Changelog](https://github.com/rust-embedded/cortex-m/blob/v0.7.7/CHANGELOG.md)
    - [Commits](https://github.com/rust-embedded/cortex-m/compare/v0.7.5...v0.7.7)
    ---
    updated-dependencies:
2023-01-05 fw: iec: Bump cortex-m from 0.7.5 to 0.7.7
2023-01-05 dependabot: Tune settings
    Only run monthly and properly prefix commit messages.
2023-01-05 build(deps): bump rp-pico from 0.2.0 to 0.6.0 in /Firmware-Rust
    Bumps [rp-pico](https://github.com/rp-rs/rp-hal-boards) from 0.2.0 to 0.6.0.
    - [Release notes](https://github.com/rp-rs/rp-hal-boards/releases)
    - [Commits](https://github.com/rp-rs/rp-hal-boards/compare/pimoroni-servo2040-0.2.0...rp-pico-0.6.0)
    ---
    updated-dependencies:
    - dependency-name: rp-pico
2023-01-05 build(deps): bump rp-pico from 0.2.0 to 0.6.0 in /Firmware-IEC
    Bumps [rp-pico](https://github.com/rp-rs/rp-hal-boards) from 0.2.0 to 0.6.0.
    - [Release notes](https://github.com/rp-rs/rp-hal-boards/releases)
    - [Commits](https://github.com/rp-rs/rp-hal-boards/compare/pimoroni-servo2040-0.2.0...rp-pico-0.6.0)
    ---
    updated-dependencies:
    - dependency-name: rp-pico
2023-02-01 fw: iec: bump cc from 1.0.78 to 1.0.79 in /Firmware-IEC
    Bumps [cc](https://github.com/rust-lang/cc-rs) from 1.0.78 to 1.0.79.
    - [Release notes](https://github.com/rust-lang/cc-rs/releases)
    - [Commits](https://github.com/rust-lang/cc-rs/compare/1.0.78...1.0.79)
    ---
    updated-dependencies:
    - dependency-name: cc
2023-03-01 fw: rust: bump cortex-m-rt from 0.7.2 to 0.7.3 in /Firmware-Rust
    Bumps [cortex-m-rt](https://github.com/rust-embedded/cortex-m) from 0.7.2 to 0.7.3.
    - [Release notes](https://github.com/rust-embedded/cortex-m/releases)
    - [Changelog](https://github.com/rust-embedded/cortex-m/blob/master/CHANGELOG.md)
    - [Commits](https://github.com/rust-embedded/cortex-m/compare/v0.7.2...v0.7.3)
    ---
    updated-dependencies:
2023-03-01 fw: iec: bump cortex-m-rt from 0.7.2 to 0.7.3 in /Firmware-IEC
    Bumps [cortex-m-rt](https://github.com/rust-embedded/cortex-m) from 0.7.2 to 0.7.3.
    - [Release notes](https://github.com/rust-embedded/cortex-m/releases)
    - [Changelog](https://github.com/rust-embedded/cortex-m/blob/master/CHANGELOG.md)
    - [Commits](https://github.com/rust-embedded/cortex-m/compare/v0.7.2...v0.7.3)
    ---
    updated-dependencies:
2023-03-01 fw: iec: bump rmodbus from 0.6.4 to 0.7.2 in /Firmware-IEC
    Bumps [rmodbus](https://github.com/alttch/rmodbus) from 0.6.4 to 0.7.2.
    - [Release notes](https://github.com/alttch/rmodbus/releases)
    - [Changelog](https://github.com/alttch/rmodbus/blob/master/CHANGELOG.md)
    - [Commits](https://github.com/alttch/rmodbus/commits/v0.7.2)
    ---
    updated-dependencies:
2023-04-01 fw: iec: bump paste from 1.0.11 to 1.0.12 in /Firmware-IEC
    Bumps [paste](https://github.com/dtolnay/paste) from 1.0.11 to 1.0.12.
    - [Release notes](https://github.com/dtolnay/paste/releases)
    - [Commits](https://github.com/dtolnay/paste/compare/1.0.11...1.0.12)
    ---
    updated-dependencies:
    - dependency-name: paste
2023-04-08 fw: iec: bump rp-pico from 0.2.0 to 0.7.0 in /Firmware-IEC
    Bumps [rp-pico](https://github.com/rp-rs/rp-hal-boards) from 0.2.0 to 0.7.0.
    - [Release notes](https://github.com/rp-rs/rp-hal-boards/releases)
    - [Commits](https://github.com/rp-rs/rp-hal-boards/commits)
    ---
    updated-dependencies:
    - dependency-name: rp-pico
2023-05-01 fw: iec: bump rmodbus from 0.6.4 to 0.7.3 in /Firmware-IEC
    Bumps [rmodbus](https://github.com/alttch/rmodbus) from 0.6.4 to 0.7.3.
    - [Release notes](https://github.com/alttch/rmodbus/releases)
    - [Changelog](https://github.com/alttch/rmodbus/blob/master/CHANGELOG.md)
    - [Commits](https://github.com/alttch/rmodbus/commits/v0.7.3)
    ---
    updated-dependencies:
2024-05-16 ci: Use dtolnay/rust-toolchain
2024-05-16 fw: iec: Fix warning about references to static mut
    References to static mut quickly lead to undefined behavior. Adjust the
    code such that no direct references to static mut variables are created.
